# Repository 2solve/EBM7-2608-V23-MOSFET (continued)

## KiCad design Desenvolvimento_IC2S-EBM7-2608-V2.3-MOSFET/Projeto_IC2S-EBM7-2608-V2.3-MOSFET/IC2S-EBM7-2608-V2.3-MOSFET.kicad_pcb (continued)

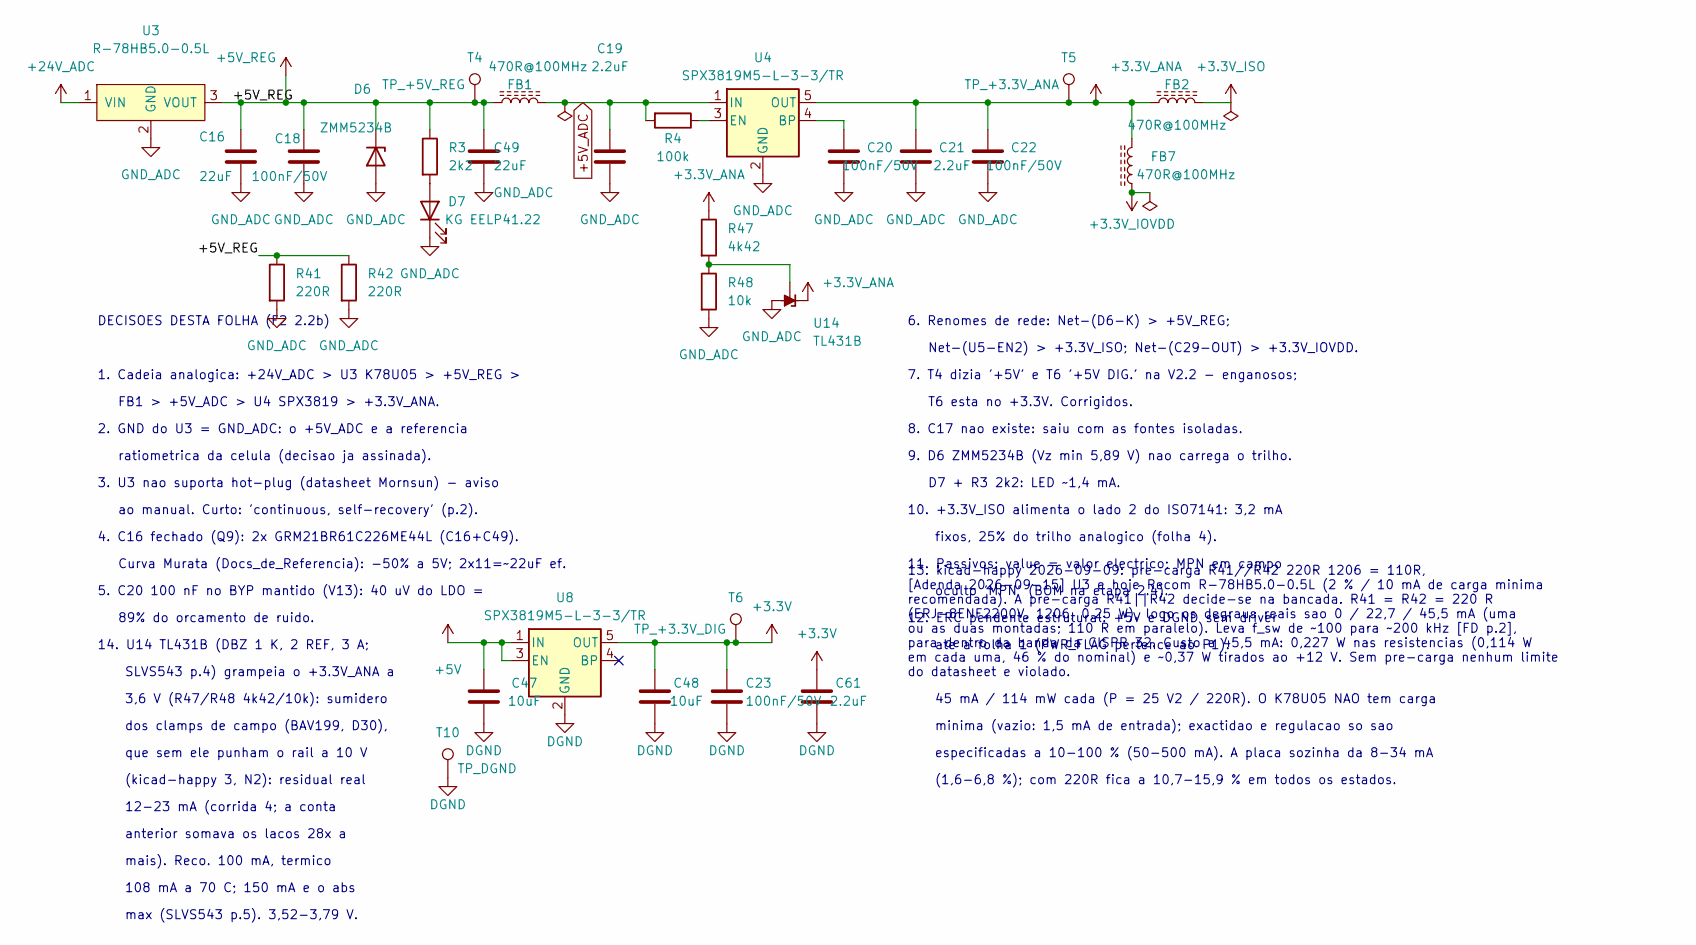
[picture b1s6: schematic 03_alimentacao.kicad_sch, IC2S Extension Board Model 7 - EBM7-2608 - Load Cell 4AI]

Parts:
C16, C49: 22uF; C_0805_2012Metric; MPN CL21A226KOQNNNG
C18, C20, C22, C23: 100nF/50V; 0603C; MPN C1608X7R1H104K080AA
C19, C21, C61: 2.2uF; 0603C; MPN C1608X5R1E225K080AB
C47, C48: 10uF; 0603C; MPN 0603YD106KAT2A
D6: ZMM5234B; SOD-80C; MPN ZMM5234B
D7: KG EELP41.22; 0603LED; MPN KG EELP41.22-PHRH-35-A8J8-20-R18
FB1, FB2, FB7: 470R@100MHz; 0603FB; MPN BLM18PG471SN1D
R3: 2k2; 0603R; MPN RC0603FR-072K2L
R4: 100k; 0603R; MPN CRCW0603100KFKEA
R41, R42: 220R; 1206R; MPN RC1206FR-07220RL
R47: 4k42; 0603R; MPN RMCF0603FT4K42
R48: 10k; 0603R; MPN RC0603FR-0710KL
T4: TP_+5V_REG; TestPad_Via
T5: TP_+3.3V_ANA; TestPad_Via
T6: TP_+3.3V_DIG; TestPad_Via
T10: TP_DGND; TestPad_Via
U3: R-78HB5.0-0.5L; R-78HBxx-0.5L_SIP-3H; MPN R-78HB5.0-0.5L
U4, U8: SPX3819M5-L-3-3/TR; SOT-23-5; MPN SPX3819M5-L-3-3/TR
U14: TL431B; SOT23-3; MPN TL431BQDBZR

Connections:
+3.3V: C23.1, C48.2, C61.2, T6.1 (1_1), U8.5 (OUT); also elsewhere on the board
+3.3V_IOVDD: FB7.1; also elsewhere on the board
+3.3V_ISO: FB2.2; also elsewhere on the board
+5V: C47.2, U8.1 (IN), U8.3 (EN); also elsewhere on the board
+5V_ADC: C19.2, FB1.2, R4.2, U4.1 (IN); also elsewhere on the board
+5V_REG: C16.2, C18.2, C49.2, D6.1 (K), FB1.1, R3.1, R41.1, R42.1, T4.1 (1_1), U3.3 (VOUT)
+24V_ADC: U3.1 (VIN); also elsewhere on the board
DGND: C23.2, C47.1, C48.1, C61.1, T10.1 (1_1), U8.2 (GND); also elsewhere on the board
unnamed: D7.2 (A), R3.2
unnamed: C20.2, U4.4 (BP)
unnamed: R4.1, U4.3 (EN)
unnamed: R47.2, R48.1, U14.2 (REF)

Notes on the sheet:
dos clamps de campo (BAV199, D30),
mais). Reco. 100 mA, termico
ate a folha 1 (PWR_FLAG pertence ao P1).
8. C17 nao existe: saiu com as fontes isoladas.
minima (vazio: 1,5 mA de entrada); exactidao e regulacao so sao
7. T4 dizia '+5V' e T6 '+5V DIG.' na V2.2 - enganosos;
6. Renomes de rede: Net-(D6-K) > +5V_REG;
3. U3 nao suporta hot-plug (datasheet Mornsun) - aviso
3,6 V (R47/R48 4k42/10k): sumidero
ratiometrica da celula (decisao ja assinada).
D7 + R3 2k2: LED ~1,4 mA.
FB1 > +5V_ADC > U4 SPX3819 > +3.3V_ANA.
que sem ele punham o rail a 10 V
4. C16 fechado (Q9): 2x GRM21BR61C226ME44L (C16+C49).
108 mA a 70 C; 150 mA e o abs
14. U14 TL431B (DBZ 1 K, 2 REF, 3 A;
anterior somava os lacos 28x a
Curva Murata (Docs_de_Referencia): -50% a 5V; 2x11=~22uF ef.
10. +3.3V_ISO alimenta o lado 2 do ISO7141: 3,2 mA
T6 esta no +3.3V. Corrigidos.
oculto 'MPN' (BOM na etapa 2.4).
13. kicad-happy 2026-09-09: pre-carga R41//R42 220R 1206 = 110R, [Adenda 2026-09-15] U3 e hoje Recom R-78HB5.0-0.5L (2 % / 10 mA de carga minima recomendada). A pre-carga R41||R42 decide-se na bancada. R41 = R42 = 220 R (ERJ-8ENF2200V, 1206, 0,25 W), logo os degraus reais sao 0 / 22,7 / 45,5 mA (um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
11. Passivos: value = valor electrico; MPN em campo
12. ERC pendente estrutural: +5V e DGND sem driver
2. GND do U3 = GND_ADC: o +5V_ADC e a referencia
(1,6-6,8 %); com 220R fica a 10,7-15,9 % em todos os estados.
fixos, 25% do trilho analogico (folha 4).
5. C20 100 nF no BYP mantido (V13): 40 uV do LDO =
1. Cadeia analogica: +24V_ADC > U3 K78U05 > +5V_REG >
Net-(U5-EN2) > +3.3V_ISO; Net-(C29-OUT) > +3.3V_IOVDD.
DECISOES DESTA FOLHA (F2 2.2b)
SLVS543 p.4) grampeia o +3.3V_ANA a
(kicad-happy 3, N2): residual real
45 mA / 114 mW cada (P = 25 V2 / 220R). O K78U05 NAO tem carga
ao manual. Curto: 'continuous, self-recovery' (p.2).
9. D6 ZMM5234B (Vz min 5,89 V) nao carrega o trilho.
12-23 mA (corrida 4; a conta
especificadas a 10-100 % (50-500 mA). A placa sozinha da 8-34 mA
89% do orcamento de ruido.
max (SLVS543 p.5). 3,52-3,79 V.

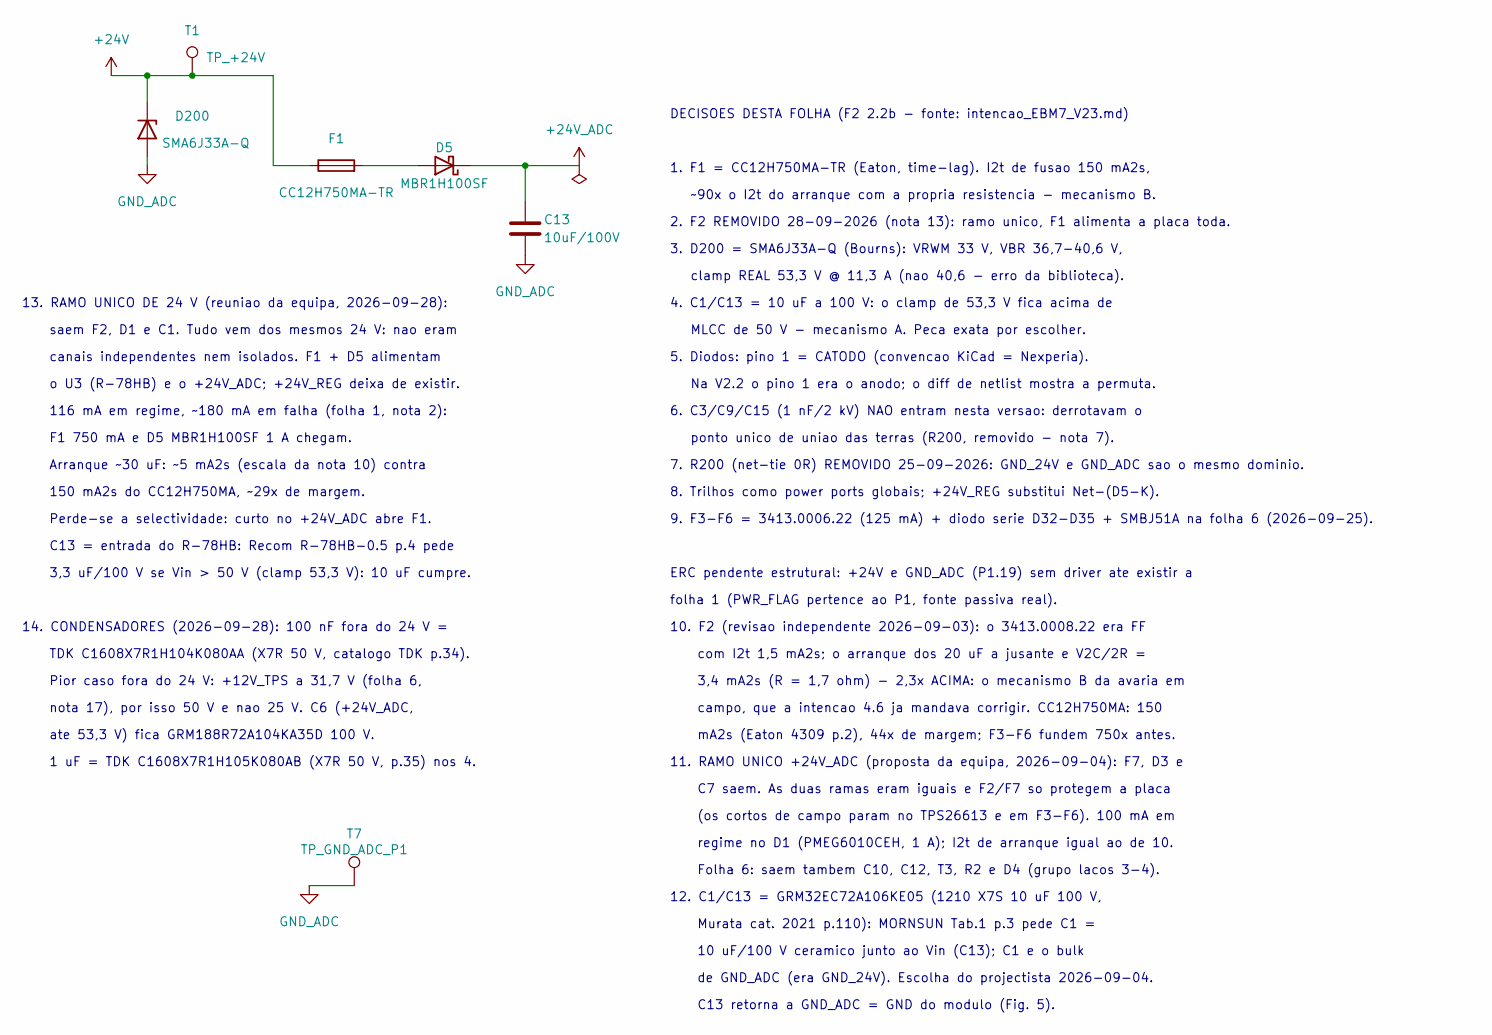
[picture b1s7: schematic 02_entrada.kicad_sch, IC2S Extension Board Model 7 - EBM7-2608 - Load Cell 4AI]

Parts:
C13: 10uF/100V; C_1210_3225Metric; MPN GRM32EC72A106ME05L
D5: MBR1H100SF; SOD123; MPN MBR1H100SFT3G
D200: SMA6J33A-Q; DO-214; MPN SMA6J33A-Q
F1: CC12H750MA-TR; 1206F; MPN CC12H750MA-TR
T1: TP_+24V; TestPad_Via
T7: TP_GND_ADC_P1; TestPad_Via

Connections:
+24V: D200.1 (K), F1.1, T1.1 (1_1); also elsewhere on the board
+24V_ADC: C13.1, D5.1 (K); also elsewhere on the board
unnamed: D5.2 (A), F1.2

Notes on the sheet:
8. Trilhos como power ports globais; +24V_REG substitui Net-(D5-K).
Murata cat. 2021 p.110): MORNSUN Tab.1 p.3 pede C1 =
5. Diodos: pino 1 = CATODO (convencao KiCad = Nexperia).
Folha 6: saem tambem C10, C12, T3, R2 e D4 (grupo lacos 3-4).
~90x o I2t do arranque com a propria resistencia - mecanismo B.
MLCC de 50 V - mecanismo A. Peca exata por escolher.
12. C1/C13 = GRM32EC72A106KE05 (1210 X7S 10 uF 100 V,
7. R200 (net-tie 0R) REMOVIDO 25-09-2026: GND_24V e GND_ADC sao o mesmo dominio.
com I2t 1,5 mA2s; o arranque dos 20 uF a jusante e V2C/2R =
4. C1/C13 = 10 uF a 100 V: o clamp de 53,3 V fica acima de
6. C3/C9/C15 (1 nF/2 kV) NAO entram nesta versao: derrotavam o
C13 retorna a GND_ADC = GND do modulo (Fig. 5).
de GND_ADC (era GND_24V). Escolha do projectista 2026-09-04.
10. F2 (revisao independente 2026-09-03): o 3413.0008.22 era FF
ponto unico de uniao das terras (R200, removido - nota 7).
9. F3-F6 = 3413.0006.22 (125 mA) + diodo serie D32-D35 + SMBJ51A na folha 6 (2026-09-25).
folha 1 (PWR_FLAG pertence ao P1, fonte passiva real).
campo, que a intencao 4.6 ja mandava corrigir. CC12H750MA: 150
3. D200 = SMA6J33A-Q (Bourns): VRWM 33 V, VBR 36,7-40,6 V,
clamp REAL 53,3 V @ 11,3 A (nao 40,6 - erro da biblioteca).
10 uF/100 V ceramico junto ao Vin (C13); C1 e o bulk
1. F1 = CC12H750MA-TR (Eaton, time-lag). I2t de fusao 150 mA2s,
mA2s (Eaton 4309 p.2), 44x de margem; F3-F6 fundem 750x antes.
ERC pendente estrutural: +24V e GND_ADC (P1.19) sem driver ate existir a
2. F2 REMOVIDO 28-09-2026 (nota 13): ramo unico, F1 alimenta a placa toda.
3,4 mA2s (R = 1,7 ohm) - 2,3x ACIMA: o mecanismo B da avaria em
Na V2.2 o pino 1 era o anodo; o diff de netlist mostra a permuta.
C7 saem. As duas ramas eram iguais e F2/F7 so protegem a placa
11. RAMO UNICO +24V_ADC (proposta da equipa, 2026-09-04): F7, D3 e
(os cortos de campo param no TPS26613 e em F3-F6). 100 mA em
DECISOES DESTA FOLHA (F2 2.2b - fonte: intencao_EBM7_V23.md)
regime no D1 (PMEG6010CEH, 1 A); I2t de arranque igual ao de 10.
13. RAMO UNICO DE 24 V (reuniao da equipa, 2026-09-28):
saem F2, D1 e C1. Tudo vem dos mesmos 24 V: nao eram
canais independentes nem isolados. F1 + D5 alimentam
o U3 (R-78HB) e o +24V_ADC; +24V_REG deixa de existir.
116 mA em regime, ~180 mA em falha (folha 1, nota 2):
F1 750 mA e D5 MBR1H100SF 1 A chegam.
Arranque ~30 uF: ~5 mA2s (escala da nota 10) contra
150 mA2s do CC12H750MA, ~29x de margem.

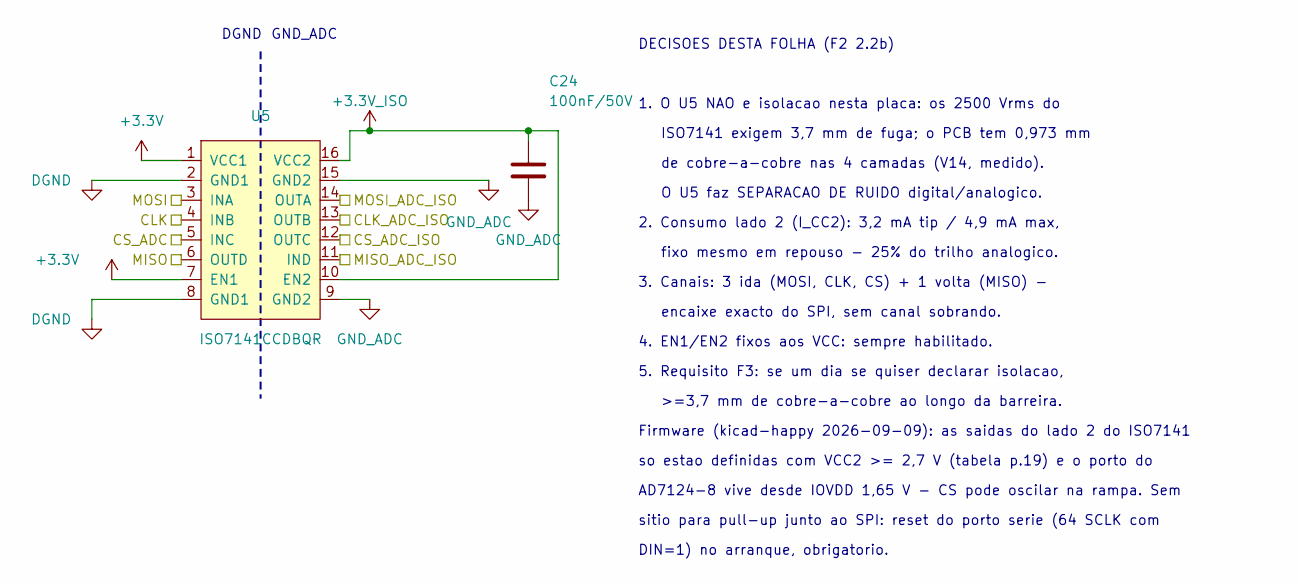
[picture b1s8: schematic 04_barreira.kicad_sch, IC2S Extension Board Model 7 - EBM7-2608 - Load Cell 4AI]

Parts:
C24: 100nF/50V; 0603C; MPN C1608X7R1H104K080AA
U5: ISO7141CCDBQR; SSOP16-4.9x3.9mm; MPN ISO7141CCDBQR

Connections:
+3.3V: U5.1 (VCC1), U5.7 (EN1); also elsewhere on the board
+3.3V_ISO: C24.1, U5.10 (EN2), U5.16 (VCC2); also elsewhere on the board
/4 Barreira digital/CLK_ADC_ISO: U5.13 (OUTB); also elsewhere on the board
/4 Barreira digital/CS_ADC_ISO: U5.12 (OUTC); also elsewhere on the board
/4 Barreira digital/MISO_ADC_ISO: U5.11 (IND); also elsewhere on the board
/4 Barreira digital/MOSI_ADC_ISO: U5.14 (OUTA); also elsewhere on the board
/CLK: U5.4 (INB); also elsewhere on the board
/CS_ADC: U5.5 (INC); also elsewhere on the board
/MISO: U5.6 (OUTD); also elsewhere on the board
/MOSI: U5.3 (INA); also elsewhere on the board
DGND: U5.2 (GND1), U5.8 (GND1); also elsewhere on the board

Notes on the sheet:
AD7124-8 vive desde IOVDD 1,65 V - CS pode oscilar na rampa. Sem
DECISOES DESTA FOLHA (F2 2.2b)
ISO7141 exigem 3,7 mm de fuga; o PCB tem 0,973 mm
sitio para pull-up junto ao SPI: reset do porto serie (64 SCLK com
encaixe exacto do SPI, sem canal sobrando.
de cobre-a-cobre nas 4 camadas (V14, medido).
5. Requisito F3: se um dia se quiser declarar isolacao,
2. Consumo lado 2 (I_CC2): 3,2 mA tip / 4,9 mA max,
DGND
Firmware (kicad-happy 2026-09-09): as saidas do lado 2 do ISO7141
1. O U5 NAO e isolacao nesta placa: os 2500 Vrms do
O U5 faz SEPARACAO DE RUIDO digital/analogico.
GND_ADC
4. EN1/EN2 fixos aos VCC: sempre habilitado.
3. Canais: 3 ida (MOSI, CLK, CS) + 1 volta (MISO) -
so estao definidas com VCC2 >= 2,7 V (tabela p.19) e o porto do
fixo mesmo em repouso - 25% do trilho analogico.
>=3,7 mm de cobre-a-cobre ao longo da barreira.
DIN=1) no arranque, obrigatorio.

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
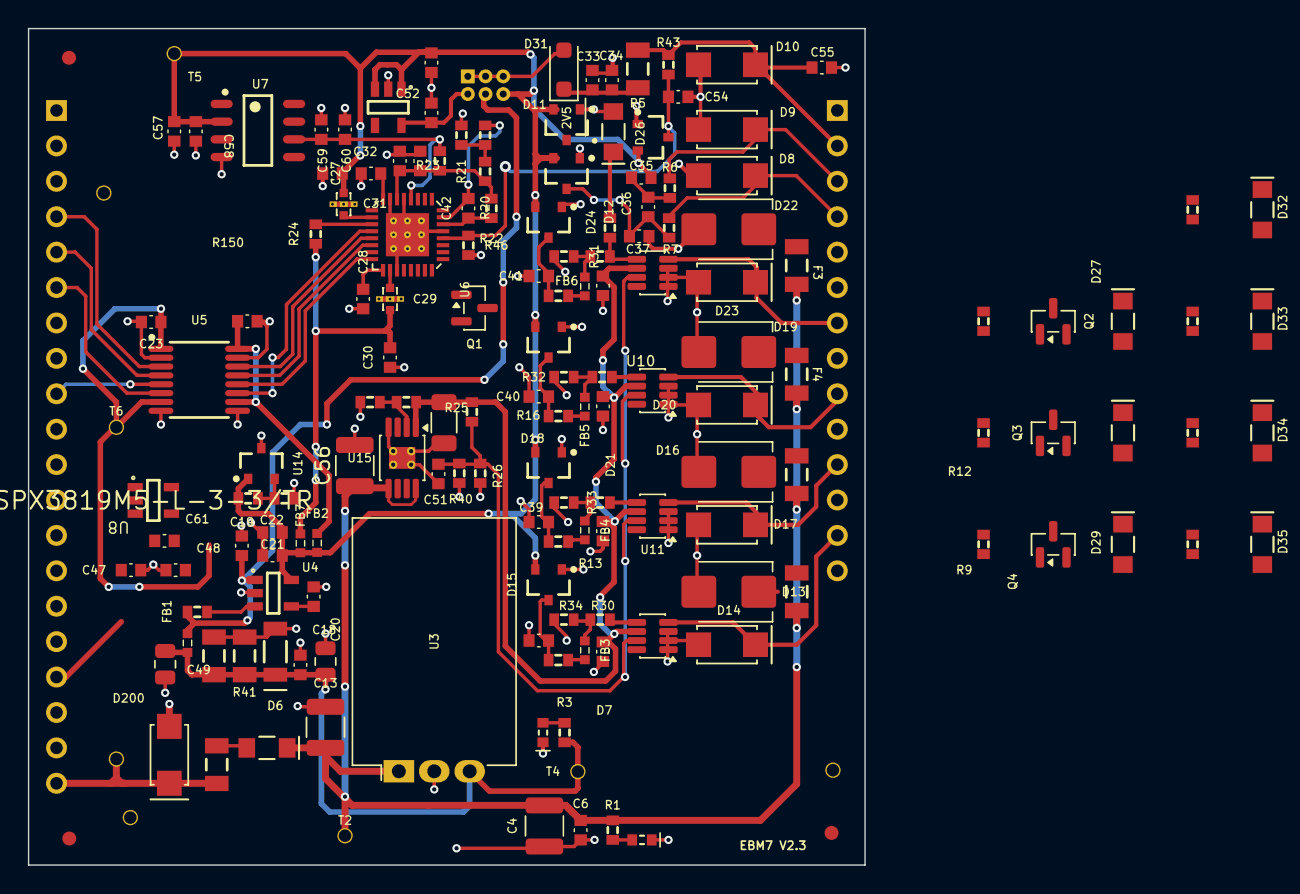
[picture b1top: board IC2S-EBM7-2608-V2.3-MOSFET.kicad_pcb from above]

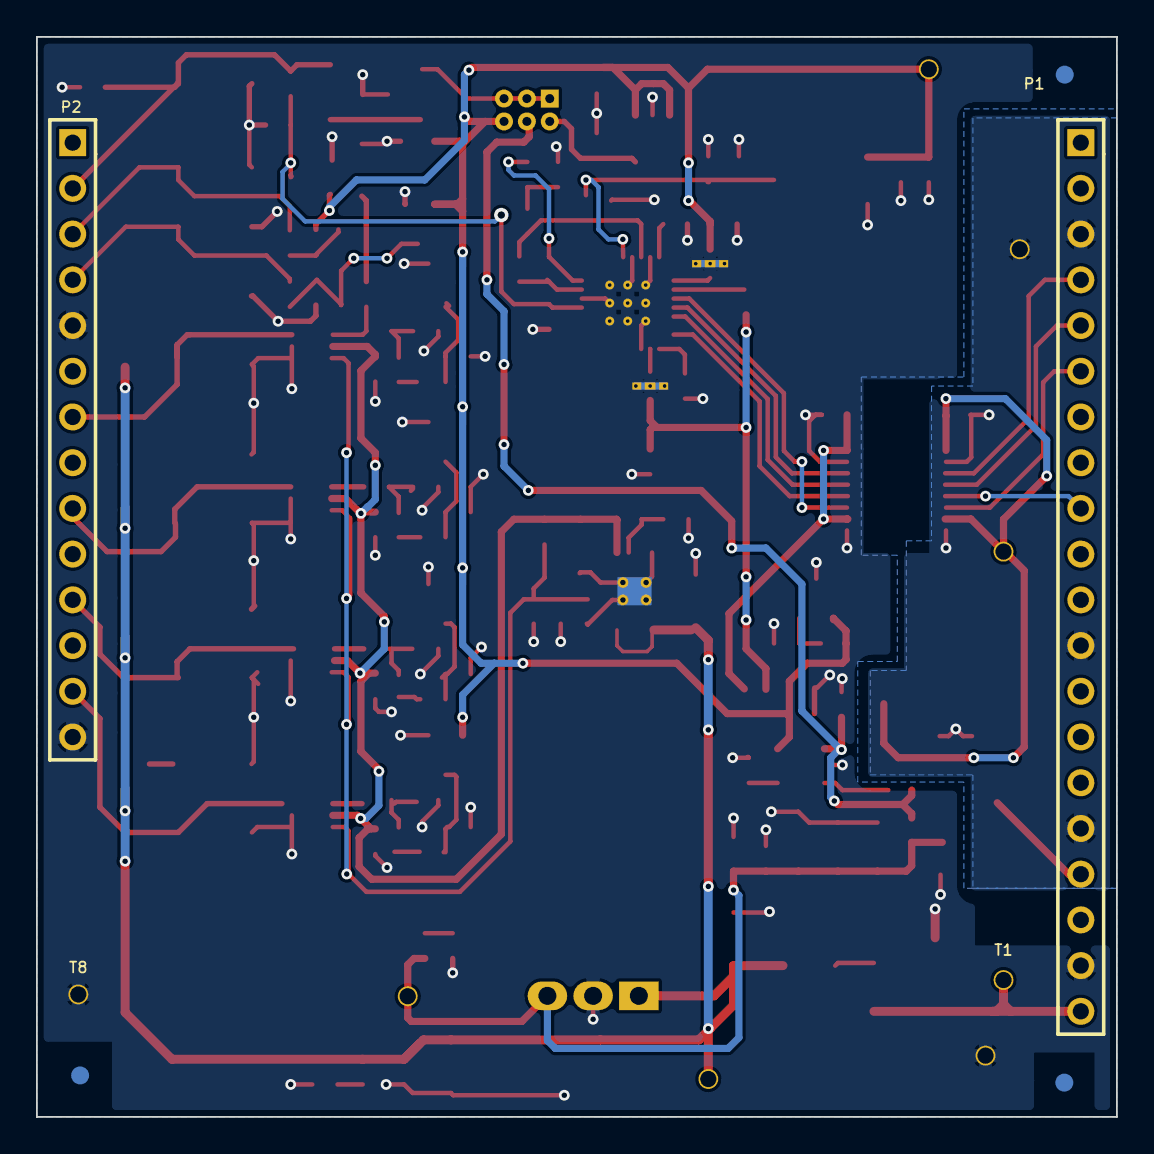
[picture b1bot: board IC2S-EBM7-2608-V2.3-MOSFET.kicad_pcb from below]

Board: 4 copper layers, 60.0 x 60.0 mm, 166 parts (4 on the bottom side), 83 nets.
